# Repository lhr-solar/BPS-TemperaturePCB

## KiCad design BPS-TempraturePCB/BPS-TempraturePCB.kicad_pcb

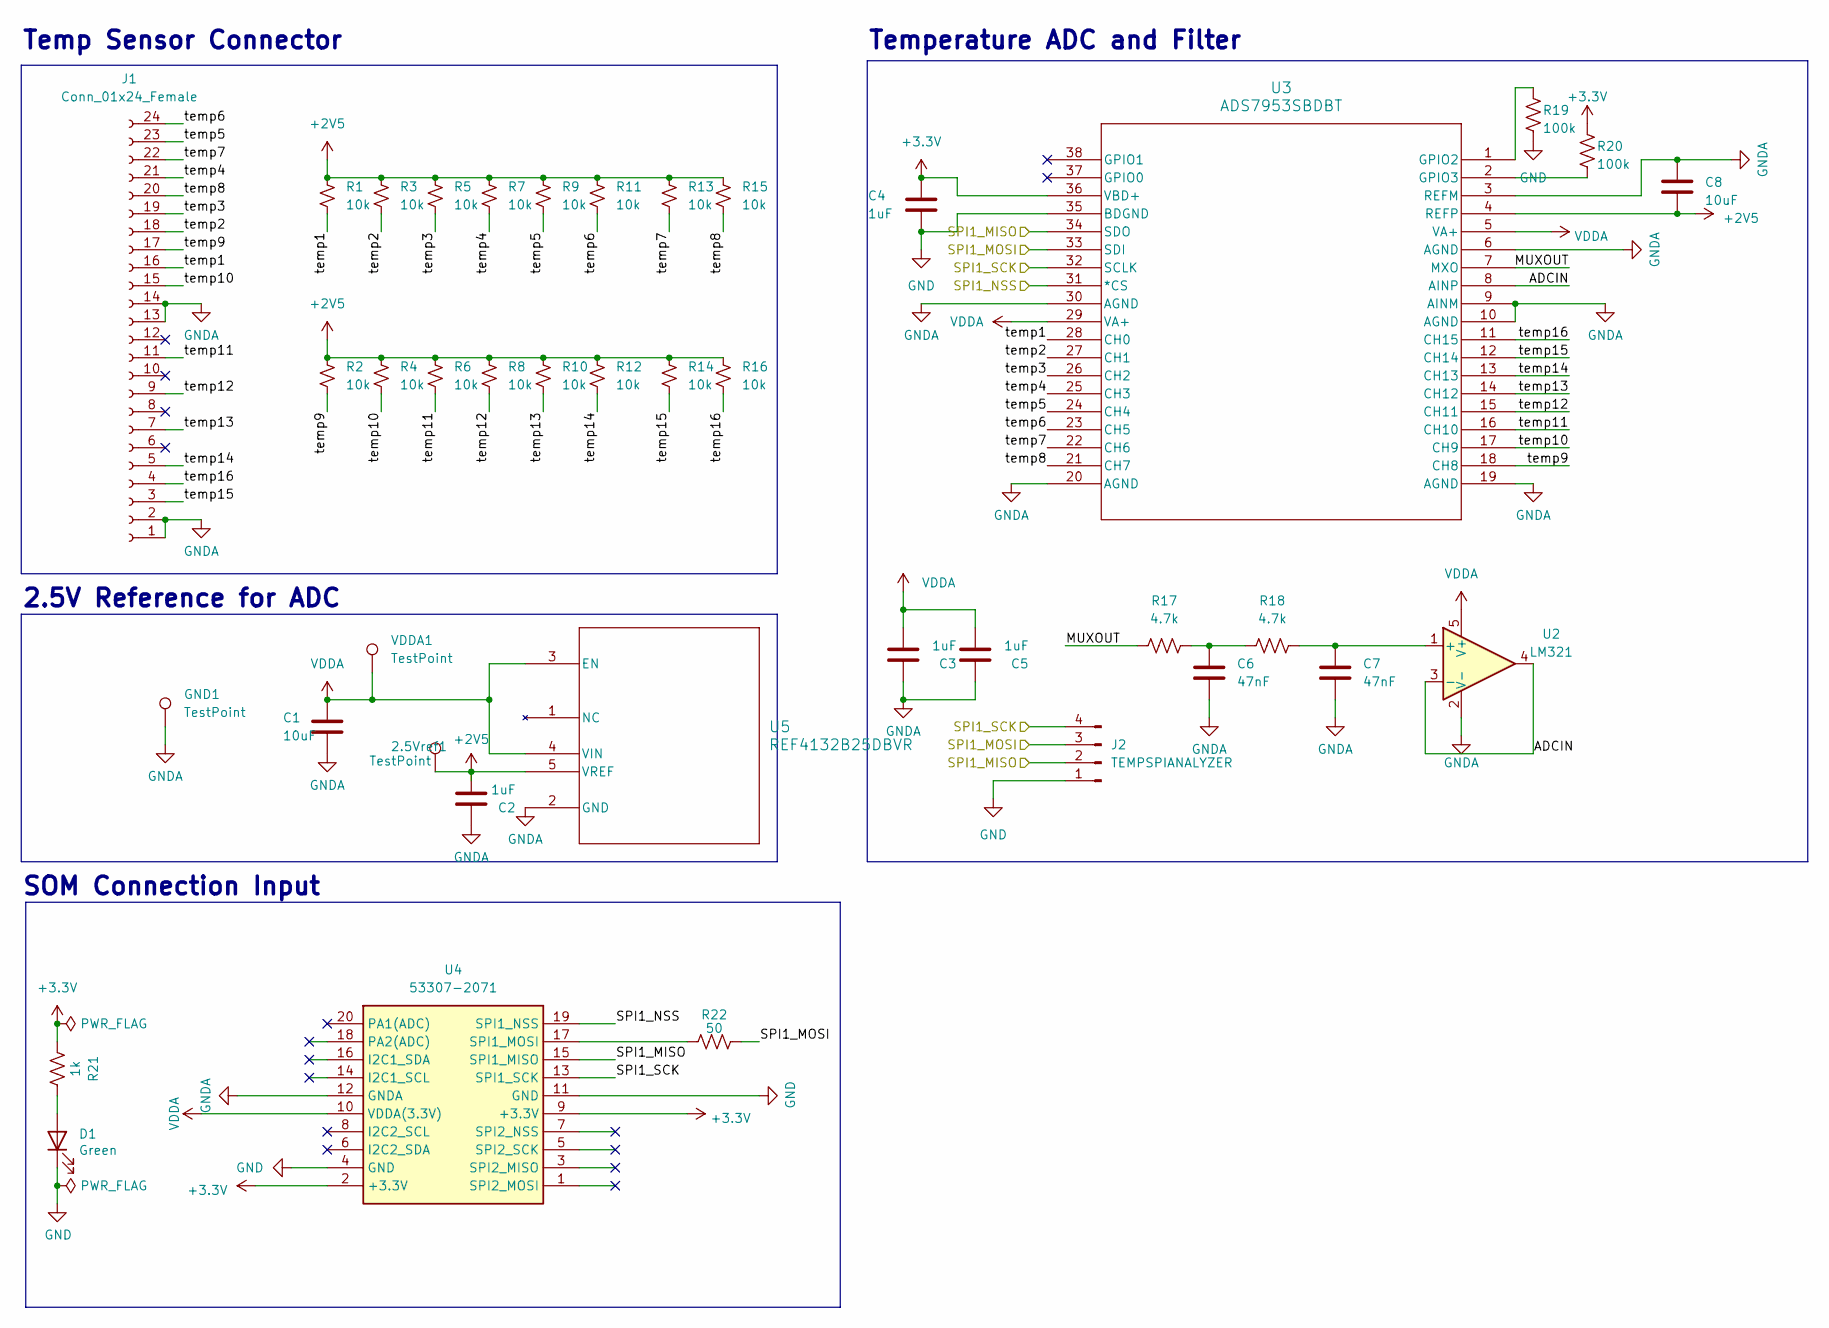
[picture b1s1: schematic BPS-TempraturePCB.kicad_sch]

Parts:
2.5Vref1: TestPoint; TestPoint_Keystone_5005-5009_Compact
C1, C8: 10uF; C_0805_2012Metric
C2, C3, C4, C5: 1uF; C_0805_2012Metric
C6, C7: 47nF; C_0805_2012Metric
D1: Green; LED_0805_2012Metric
GND1: TestPoint; TestPoint_Keystone_5005-5009_Compact
J1: Conn_01x24_Female; PinHeader_1x24_P2.54mm_Vertical
J2: TEMPSPIANALYZER; PinHeader_1x04_P2.54mm_Vertical
R1, R2, R3, R4, R5, R6, R7, R8, R9, R10, R11, R12, R13, R14, R15, R16: 10k; R_0805_2012Metric
R17, R18: 4.7k; R_0805_2012Metric
R19, R20: 100k; R_0805_2012Metric
R21: 1k; R_0805_2012Metric
R22: 50; R_0805_2012Metric
U2: LM321; SOT-23-5
U3: ADS7953SBDBT; TSSOP-38_4.4x9.7mm_P0.5mm
U4: PeripheralSOM
U5: REF4132B25DBVR; SOT-23-5_DBV_TEX
VDDA1: TestPoint; TestPoint_Keystone_5005-5009_Compact

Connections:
+2V5: 2.5Vref1.1, C2.1, C8.2, R1.2, R2.2, R3.2, R4.2, R5.2, R6.2, R7.2, R8.2, R9.2, R10.2, R11.2, R12.2, R13.2, R14.2, R15.2, R16.2, U3.4 (REFP), U5.5 (VREF)
+3.3V: C4.2, R20.1, R21.2, U3.36 (VBD+), U4.2 (+3.3V), U4.9 (+3.3V)
/ADCIN: U2.3 (-), U2.4, U3.8 (AINP)
/MUXOUT: R17.2, U3.7 (MXO)
/SPI1_MISO: J2.2, U3.34 (SDO), U4.15 (SPI1_MISO)
/SPI1_MOSI: J2.3, R22.1, U3.33 (SDI)
/SPI1_NSS: U3.31 (*CS), U4.19 (SPI1_NSS)
/SPI1_SCK: J2.4, U3.32 (SCLK), U4.13 (SPI1_SCK)
/temp1: J1.16, R1.1, U3.28 (CH0)
/temp2: J1.18, R3.1, U3.27 (CH1)
/temp3: J1.19, R5.1, U3.26 (CH2)
/temp4: J1.21, R7.1, U3.25 (CH3)
/temp5: J1.23, R9.1, U3.24 (CH4)
/temp6: J1.24, R11.1, U3.23 (CH5)
/temp7: J1.22, R13.1, U3.22 (CH6)
/temp8: J1.20, R15.1, U3.21 (CH7)
/temp9: J1.17, R2.1, U3.18 (CH8)
/temp10: J1.15, R4.1, U3.17 (CH9)
/temp11: J1.11, R6.1, U3.16 (CH10)
/temp12: J1.9, R8.1, U3.15 (CH11)
/temp13: J1.7, R10.1, U3.14 (CH12)
/temp14: J1.5, R12.1, U3.13 (CH13)
/temp15: J1.3, R14.1, U3.12 (CH14)
/temp16: J1.4, R16.1, U3.11 (CH15)
GND: C4.1, D1.1 (K), J2.1, R19.2, U3.35 (BDGND), U4.4 (GND), U4.11 (GND)
GNDA: C1.1, C2.2, C3.2, C5.2, C6.1, C7.1, C8.1, GND1.1, J1.1, J1.2, J1.13, J1.14, U2.2 (V-), U3.3 (REFM), U3.6 (AGND), U3.9 (AINM), U3.10 (AGND), U3.19 (AGND), U3.20 (AGND), U3.30 (AGND), U4.12 (GNDA), U5.2 (GND)
unnamed: C6.2, R17.1, R18.2
unnamed: D1.2 (A), R21.1
unnamed: C7.2, R18.1, U2.1 (+)
unnamed: R19.1, U3.1 (GPIO2)
unnamed: R20.2, U3.2 (GPIO3)
unnamed: R22.2, U4.17 (SPI1_MOSI)
VDDA: C1.2, C3.1, C5.1, U2.5 (V+), U3.5 (VA+), U3.29 (VA+), U4.10 (VDDA(3.3V)), U5.3 (EN), U5.4 (VIN), VDDA1.1

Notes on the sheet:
SOM Connection Input
2.5V Reference for ADC
Temperature ADC and Filter
Temp Sensor Connector

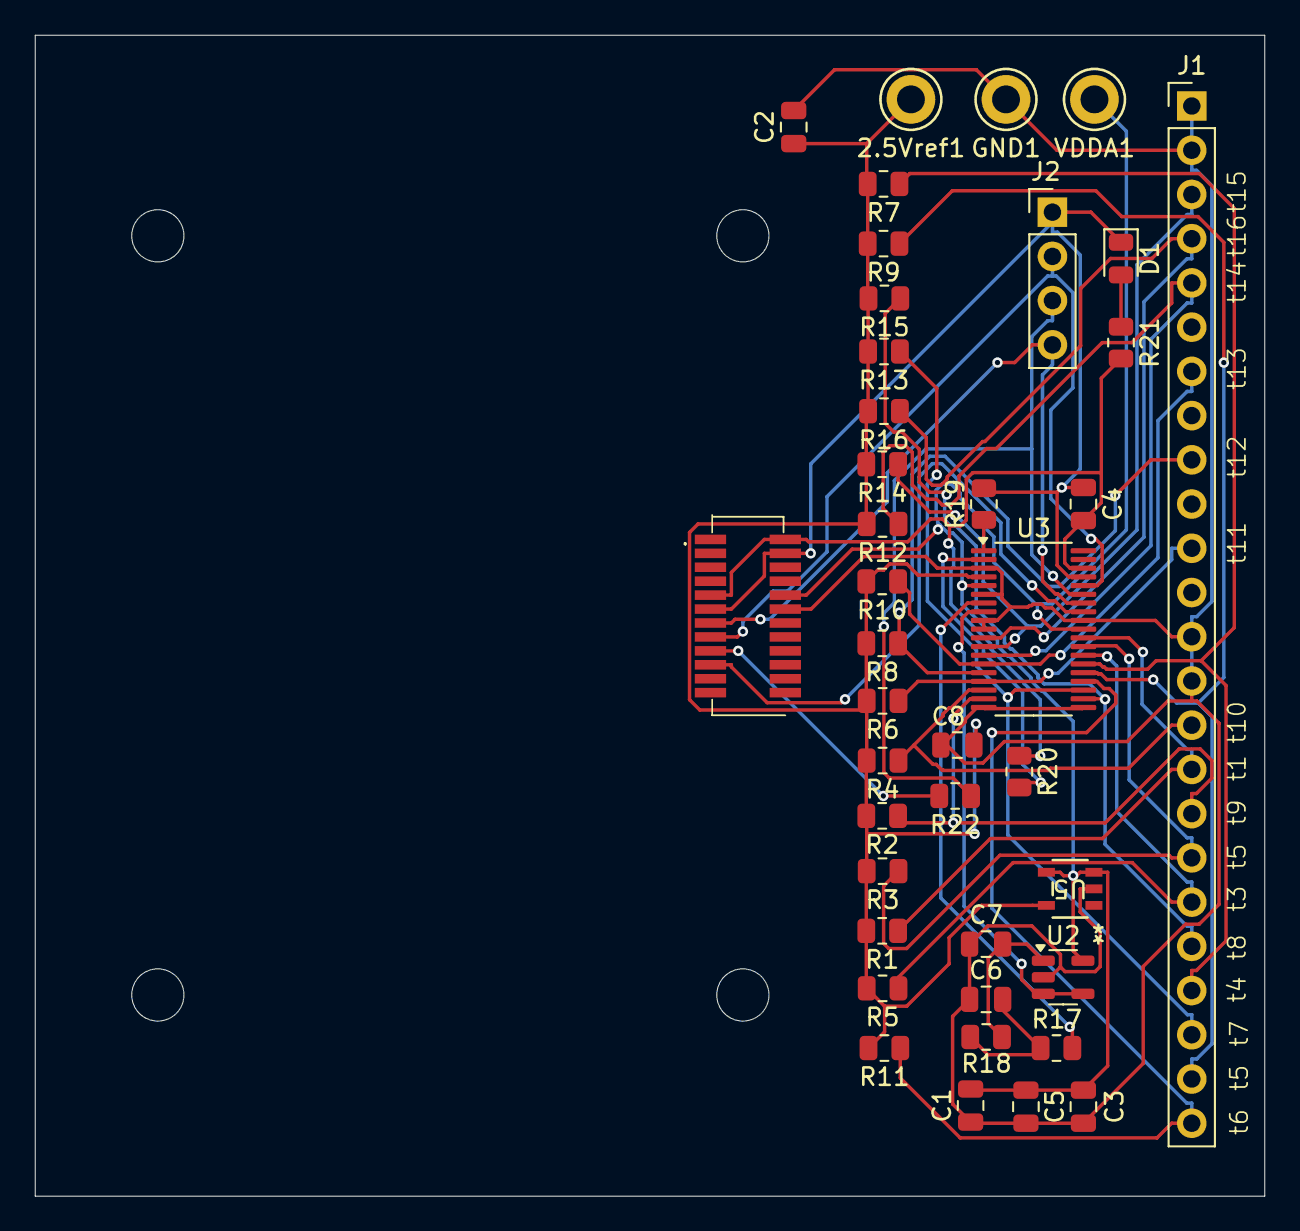
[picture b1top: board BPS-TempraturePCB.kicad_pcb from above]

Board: 2 copper layers, 70.6 x 66.7 mm, 40 parts (0 on the bottom side), 33 nets.

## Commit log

2024-10-13 mostly done, still need to connect a few traces.
2024-10-13 kicad changes
2024-10-14 Changed schematic to include new vref chip
2024-10-14 All Traces connected. Need to fix silkscreen errors and add a few more test points
2024-10-14 added silkscreen for temprature pinheaders and testpoint for analog vdd and analog ground.
2024-10-14 Fixed Missing ground connection
2024-10-14 Production zip
2024-10-15 Redid routing to be better.
